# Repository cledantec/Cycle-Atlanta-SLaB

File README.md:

Cycle Atlanta: Seeing Like a Bike
================
[Atlanta's Data Science for Social Good (DSSG) 2017](http://dssg-atl.io/)
----------

The Cycle Atlanta project aims to create sensor systems that allow a bike to "see" its environment and collect data as a participatory effort to help the City of Atlanta make informed decisions about biking infrastructures. The team from Atlanta's Data Science for Social Good 2017 Summer program particularly worked on (1) reverse engineering all the prototypes developed separately by the LMC6650 team and consolidating all sensors into two microcontoller units (Raspberry Pi and Arduino) using the Master-Slave architecture; (2) identifying hardware/software bugs/flaws and refining systems iteratively; (3) implementing failure-tolerence techniques; (4) classifying environmental factors (to detect semantci-level objects) after collecting data using GoPro, voice recorders, and sensors; and (5) visualizing and analyzing the collected data using 3D models and machine learning techniques. 

## Documentations
* [System Overview](DSSG2017_doc/overview.md)
* [Hardware Systems (Electrical Devices and Circuits)](DSSG2017_doc/hardware.md)
* [Software Systems (Server Configurations and Scripts)](DSSG2017_doc/software.md)
* [Cases Design](DSSG2017_doc/cases.md)
* [Data Visualization (3D)](DSSG2017_doc/dataviz.md)
* [Data Analysis](DSSG2017_doc/data.md)
* [Backlog (Issues and Solutions)](DSSG2017_doc/backlog.md)

## Credits (DSSG)
### PI:
* [Dr. Christopher Le Dantec](https://ledantec.net/)

### DSSG Fellows:
* [Javier Argota](http://jard.us)
* [Myeong Lee](http://myeonglee.com)
* [Noel Mannariat](mailto:noelmannariat@gmail.com)
* [Erica Pantoja](mailto:ericapantoja1190@gmail.com)

### Special Thanks To:
* Dr. Kari Watkins
* Mariam Asad
* Bijan Tehrani
* Raj Lal
* Michael Vogel
* Bradley Rittenhouse

******

## [LMC6650: Seeing Like a Bike](http://ledantec.net/teaching/lmc-6650-spring-2017/)
### Spring 2017 Georgia Tech

LMC6650 students designed a custom PCB board for gas sensors, developed the Air Quality module and a data collection server on Raspberry Pi using RestAPIs, and implemented the proximity/serface quality sensor functionalities using Rapsberry Pi and Arduino. 

## Equipment used
* [Raspberry Pi](http://raspberrypi.org)
* [Arduino Uno](https://www.arduino.cc/en/Main/arduinoBoardUno)
* [Matrix One Creator](http://creator.matrix.one)
* [Anker 26800 mAh portable power bank](https://www.amazon.com/Anker-PowerCore-Portable-Double-Speed-Recharging/dp/B01JIWQPMW)
* [Knowles BU21771 contact microphone](www.digikey.com/product-detail/en/knowles/BU-21771-000/423-1004-ND/458515)
* Dimension ST768 for 3D printing

## Credits (LMC6650)
* **Air Quality team**: [Orianna Ott](https://www.linkedin.com/in/orianaott/) , [Lorina Navarro](https://www.linkedin.com/in/lmnavarro/) , [Reuben Fishback](https://www.linkedin.com/in/reuben-fishback-a4b31085/)
* **Proximity team**: [Sharon Ang](https://www.linkedin.com/in/sharon-ang/) , [Aastha Jalan](https://www.linkedin.com/in/aasthajalan/) , [Nikhil Soraba](https://www.linkedin.com/in/nikhil-soraba/)
* **Surface Quality team**: [Nene Igietseme](https://www.linkedin.com/in/nene-igietseme-19b65125/) , [Kristin Hare](https://www.linkedin.com/in/kristin-hare/) , [Shruti Dalvi](https://www.linkedin.com/in/shruti-dalvi/) , [Jayanth Mohana Krishna](https://linkedin.com/in/jayanthm)

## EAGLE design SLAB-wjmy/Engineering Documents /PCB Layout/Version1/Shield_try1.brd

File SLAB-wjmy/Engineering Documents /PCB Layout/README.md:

xTwo versions of the PCB designs are in the &quot;PCB Layout&quot; Folder.

You may download Eagle CAD software from AutoCAD and open it from the software.

This PCB is to provide stable connection from the micro-controller to Lidars. Version 1.0 used PWM transmission; Version 2.0 used I2C communication protocol. It is believed that Version 2.0 can measure much more accurately. However, due to the shelter-in-place situation, the testing was not able to conduct.

Version 1.0 - The original version that was printed and tested.

Pros: 1) Compact; 2) Easy to manufacture

Cons: 1) Lower sampling rate; 2) Power issue; 3) Wiring harness

Version 2.0 - The improved version that was designed by WJMY. The PCB layout was validated by the Electronics lab at Georgia Tech Mechanical Engineering Department.

Pros: 1) Estimated run time: 6 hours; 2) Easy assembly and disassembly;

3) Faster sampling rate

Cons: 1) Relatively more difficult to manufacture.

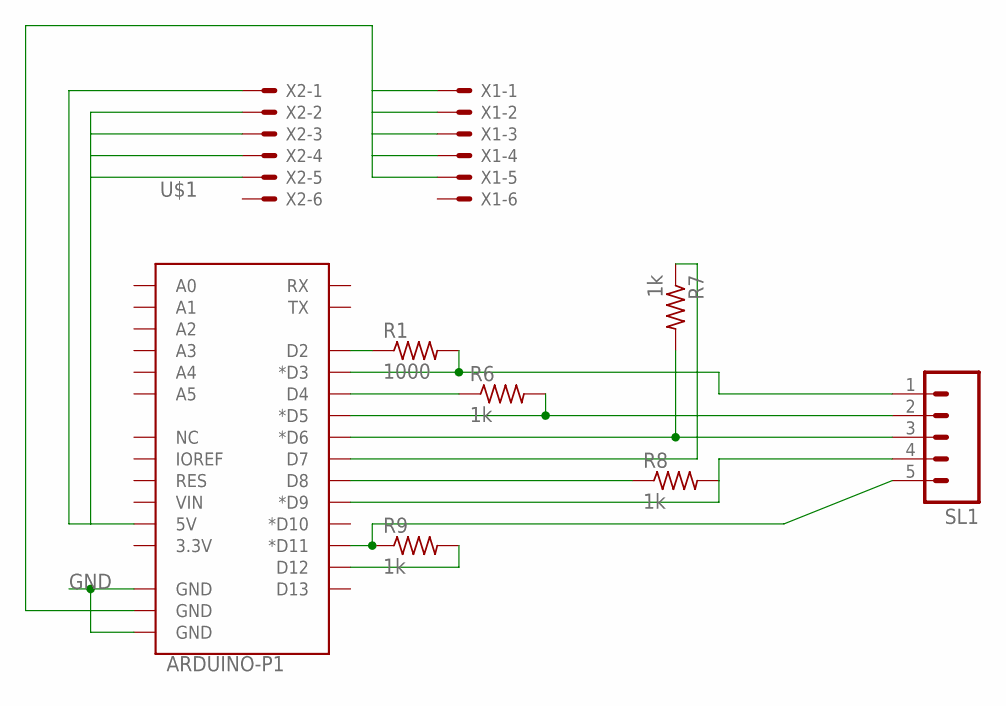
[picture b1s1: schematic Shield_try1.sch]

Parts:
R1: 1000; R0805
R6, R7, R8, R9: 1k; R0805
SL1: M05; 05P
U$1: ARDUINO-P1
X1, X2: 22-23-2061

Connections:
GND: U$1.GND@0 (GND), U$1.GND@1 (GND), U$1.GND@2 (GND), X1.1, X1.2, X1.3, X1.4, X1.5
unnamed: R1.2, SL1.1, U$1.D3 (*D3)
unnamed: R7.2, SL1.3, U$1.D6 (*D6)
unnamed: R6.1, U$1.D4
unnamed: R6.2, SL1.2, U$1.D5 (*D5)
unnamed: R7.1, U$1.D7
unnamed: R8.1, U$1.D8
unnamed: R8.2, SL1.4, U$1.D9 (*D9)
unnamed: R9.1, SL1.5, U$1.D11 (*D11)
unnamed: R9.2, U$1.D12
unnamed: R1.1, U$1.D2
unnamed: U$1.5V, X2.1, X2.2, X2.3, X2.4, X2.5

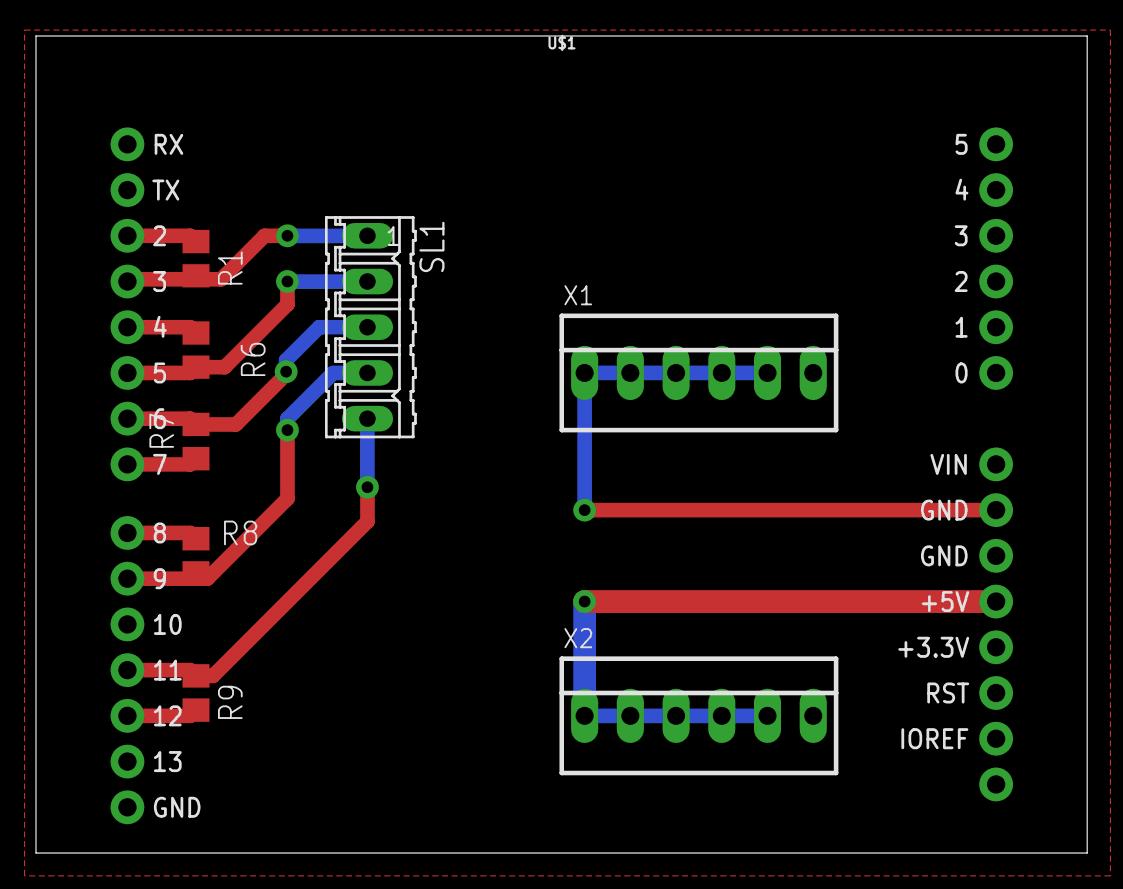
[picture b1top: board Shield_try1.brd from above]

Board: 2 copper layers, 58.4 x 45.4 mm, 9 parts (0 on the bottom side), 12 nets.

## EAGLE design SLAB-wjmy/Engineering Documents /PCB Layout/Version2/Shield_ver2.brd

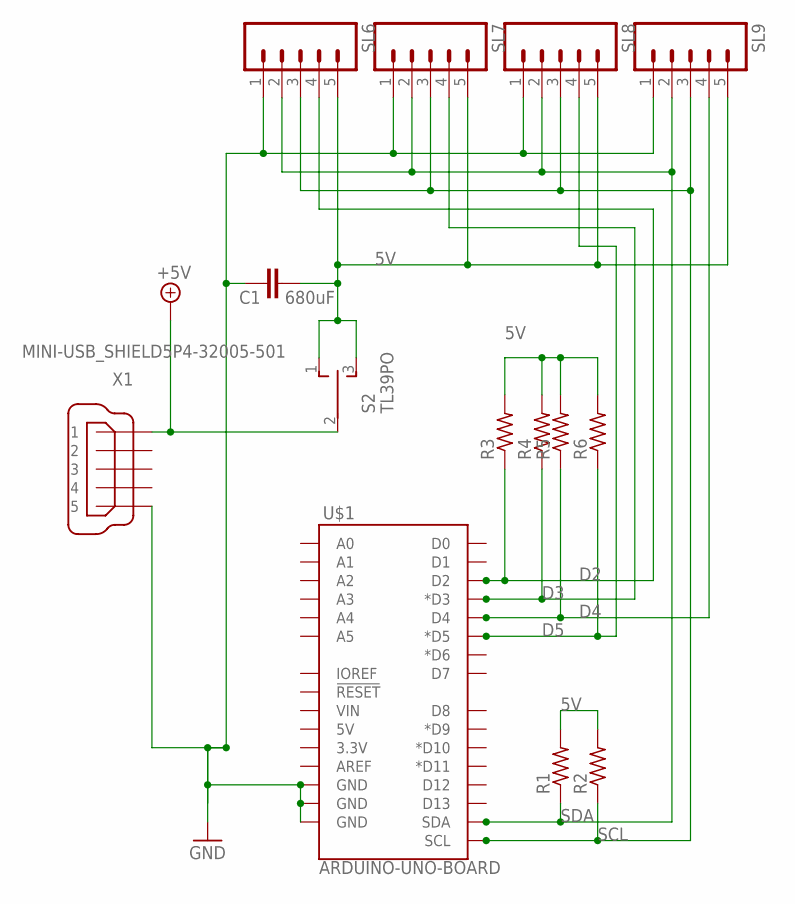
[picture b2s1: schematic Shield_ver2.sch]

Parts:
C1: 680uF; C5B2.5
R1, R2, R3, R4, R5, R6: R-US_R0805; R0805
S2: TL39PO; TL3XPO
SL6, SL7, SL8, SL9: M05; 05P
U$1: ARDUINO-UNO-BOARD
X1: MINI-USB_SHIELD5P4-32005-501; 32005-501

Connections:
5V: C1.2, R1.2, R2.2, R3.2, R4.2, R5.2, R6.2, S2.1 (O), S2.3 (S), SL6.5, SL7.5, SL8.5, SL9.5
+5V: S2.2, X1.1
D2: R3.1, SL6.4, U$1.D2
D3: R4.1, SL7.4, U$1.D3 (*D3)
D4: R5.1, SL9.4, U$1.D4
D5: R6.1, SL8.4, U$1.D5 (*D5)
GND: C1.1, SL6.1, SL7.1, SL8.1, SL9.1, U$1.GND@1 (GND), U$1.GND@2 (GND), U$1.GND@3 (GND), X1.5
SCL: R2.1, SL6.3, SL7.3, SL8.3, SL9.3, U$1.SCL
SDA: R1.1, SL6.2, SL7.2, SL8.2, SL9.2, U$1.SDA

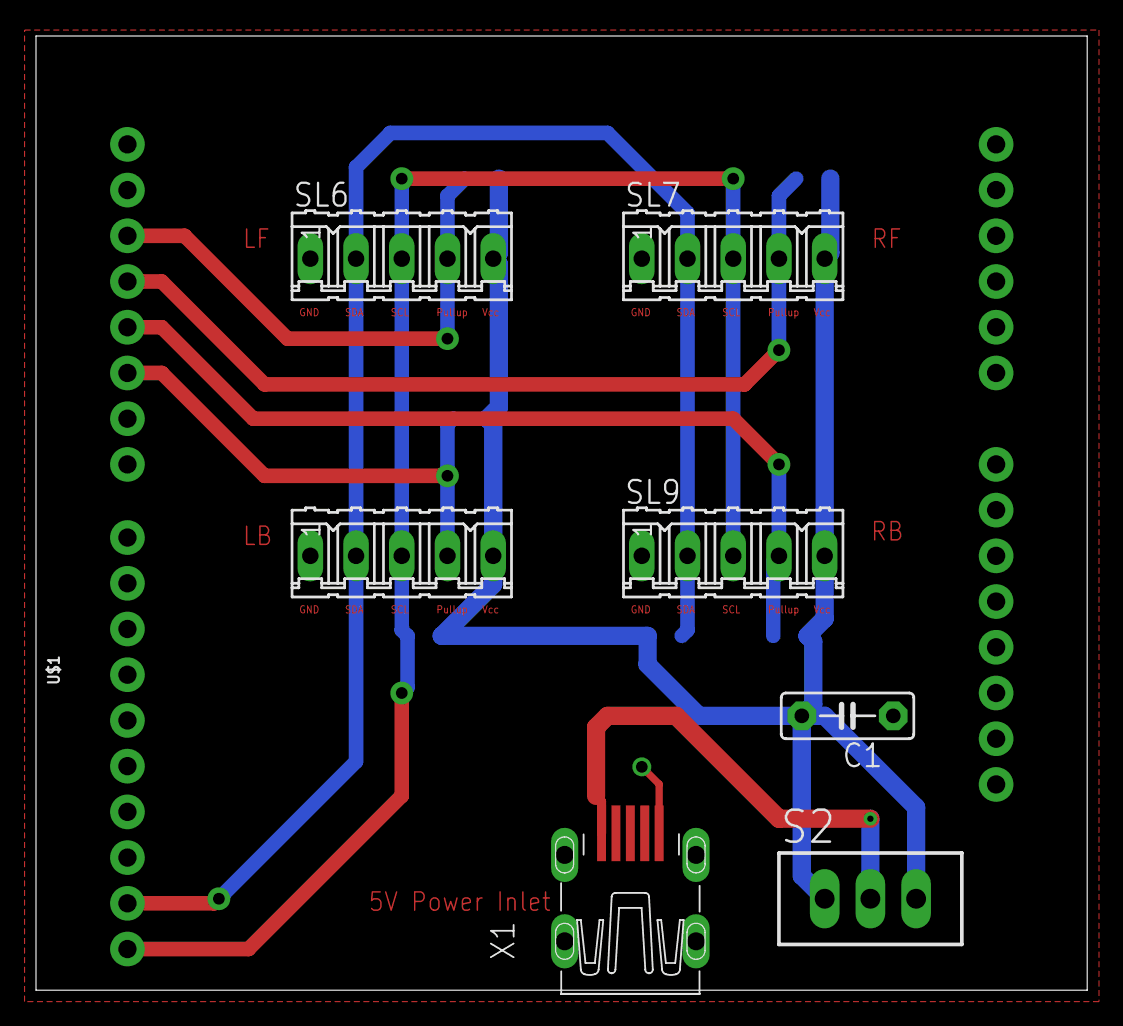
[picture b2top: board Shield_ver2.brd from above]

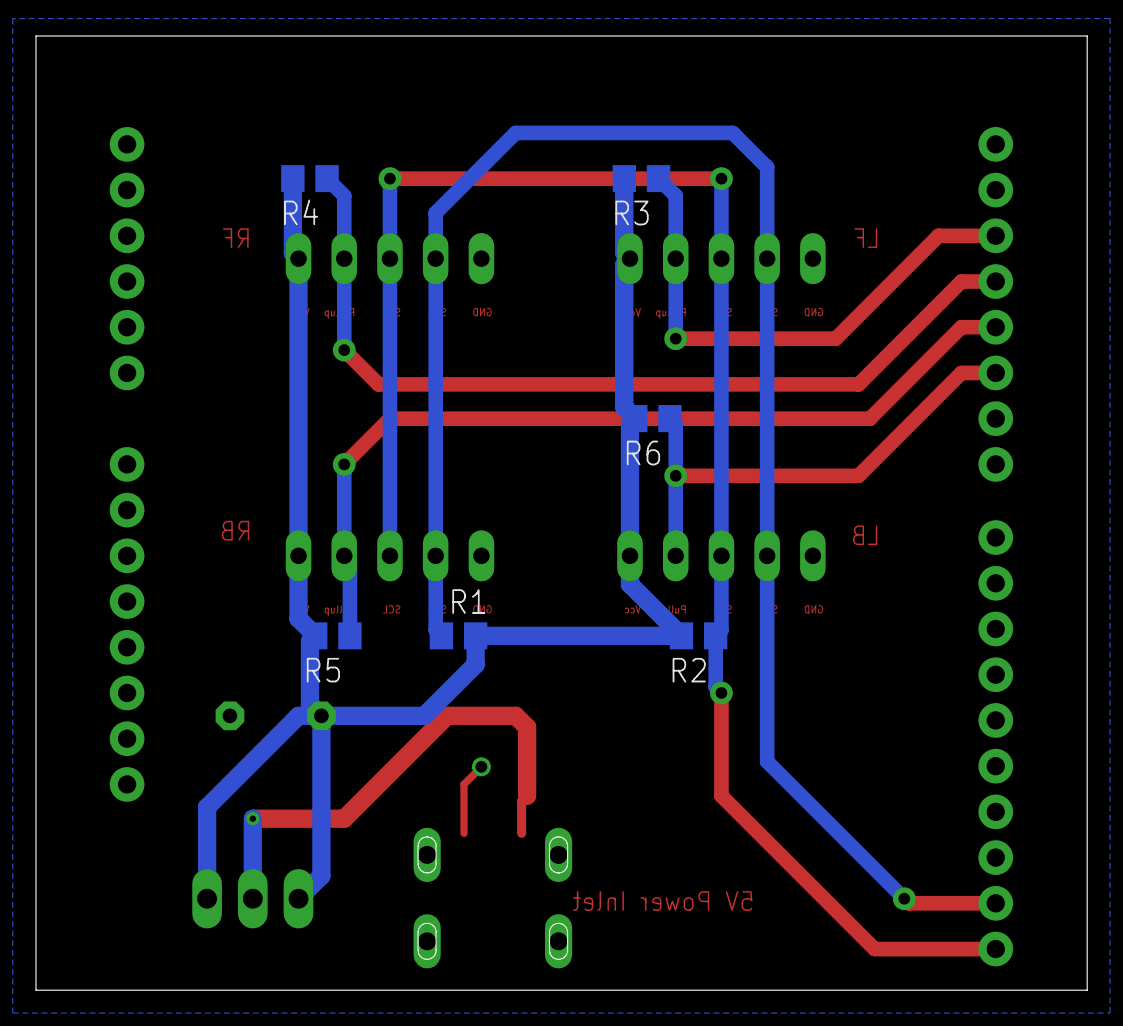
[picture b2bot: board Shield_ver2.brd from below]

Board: 2 copper layers, 58.4 x 53.0 mm, 14 parts (6 on the bottom side), 9 nets.

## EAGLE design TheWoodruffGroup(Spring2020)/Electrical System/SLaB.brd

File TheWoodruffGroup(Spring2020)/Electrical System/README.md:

# Electrical System Documentation
The electrical system includes the sensors and other electrical components used, as well as the PCB that connects them all. The electrical components include:
- 1x [Anker 5000 mAh Battery](https://www.anker.com/products/variant/powercore-5000/A1109011)
- 1x USB-A male-to-male cable
- 1x [Stewart Connector USB-A port](https://www.digikey.com/product-detail/en/stewart-connector/SS-52100-001/380-1412-ND/7902377)
- 1x On/Off Switch
- 1x Current Sensor
- 1x [Teensy 4.0 Microcontroller](https://www.pjrc.com/store/teensy40.html)
- 4x [Garmin LIDAR-Lite v4 LEDs](https://buy.garmin.com/en-US/US/p/610275)
- 1x [Adafruit Bluefruit UART Friend](https://www.adafruit.com/product/2479)
- 2x 1.5 kΩ (pull-up) resistors
- 1x 680 μF capacitor

The current PCB was designed in Eagle 9.6.1. Since Georgia Tech's [Electronics Lab](http://www.me.gatech.edu/facilities/electronic_lab) uses Eagle, PCBs can typically be manufactured within a day of the request if Eagle \*.brd files are submitted. For information on PCB design, I recommend [this tutorial by Brian Benchoff at Hackaday](https://hackaday.com/2016/09/22/making-a-pcb-eagle-part-1/). 

## Overview of Components
### Anker 5000 mAh Battery
This battery provides power to the Teensy and all of the components; it was sized based on the estimated current consumption of the device. It was calculated that the system will draw about 442 mA of current (2 mA from Bluetooth, 85 mA from each LIDAR, 100 from Teensy), so for a half-hour ride, only 221 mAh would be needed. Anker's 5000 mAh model was selected as the smallest and cheapest option, but other options may also be viable. The battery comes with a Micro-USB cable included for charging, but the micro-USB ports that I could find all seemed too small to easily solder to a PCB, so the board has a USB-A ("normal" USB) port instead, which are easier to solder, and still cheap & easy to find. Although the Teensy has a micro-USB port on it for power, connecting directly to this would make it impossible to measure the current draw, as the current sensor must be placed in series with the power source, so power must be provided through a separate USB port. 
The battery has a minimum current draw of 50 mA. We believe that the system will draw more than that, but **this would need to be verified experimentally**. 

### USB-A male-to-male cable
Since the board uses a USB-A port, a separate USB cable must be purchased to connect the battery to the board. A smaller cable would likely be best to prevent tangling. 

### Stewart Connector USB-A port
A USB-A port was chosen instead of a Micro-USB port because they appeared to be much easier to solder to a board, but any type of USB port should work, likely requiring changes to the footprint in the PCB file. This specific port was chosen because it was the cheapest one I could find on Digi-Key, but again, any USB port should work. 
The datasheet for this part did not specify which pin corresponded to what signal, so it had to be extrapolated based on similar connectors. **It needs to be verified experimentally which pin corresponds to 5V and which pin corresponds to ground**. 

### On/Off Switch 
This is a simple power switch to turn the device on or off, so that the battery power can be conserved when not in use. Any switch that holds its state and has leads attached to it can be used. Something like [this](https://www.adafruit.com/product/1092) would be fine, but the possibility of accidentally toggling the switch should be considered too, so a sliding switch might be better. The switch itself would be on the housing, and the leads coming off it would be soldered to the board. 

### Current Sensor 
The current sensor is used to estimate the current battery level by numerically integrating the current consumed over time. We never had the opportunity to test the current sensor, so everything involving it is entirely theoretical, including the wiring. The one used in the PCB is [this one from Allegro MicroSystems](https://www.digikey.com/product-detail/en/allegro-microsystems/ACS750LCA-050/ACS750LCA-050-ND/1006488), a default option provided in Eagle, which is now discontinued. It appears to have the same footprint as [this one](https://www.digikey.com/product-detail/en/allegro-microsystems/ACS770LCB-050B-PFF-T/620-1541-5-ND/4473980), which is still active. These current sensors may be bigger than we need, as they can sense up to 50 A of current, and the voltage outputted from them might be too low to be accurately read by the Teensy. **It may be better to use a different current sensor that is more suited to the range of currents being measured, and if the voltage is still too low, it may be best to amplify it with an op-amp.** It is also possible to calculate current by placing a small known resistor in series with the power source, where the current sensor would go, and measuring the voltage across it, but it is unclear how accurate this would be, and how much this would change the dynamics of the circuit. 

### Teensy 4.0 Microcontroller
This is the microcontroller that manages all of the sensors. It is faster and more powerful than an Arduino Uno, and should be fast enough to handle all the data being gathered. User-made Eagle libraries for the Teensy can be found [here](https://www.pjrc.com/teensy/eagle_lib.html), and the one used in this design is [the one by Constantin](https://forum.pjrc.com/threads/935-Eagle-library-with-Teensy-3-0-footprint?p=20178&viewfull=1#post20178) ("Teensy_3_and_LC_Series_Boards_v1.4.zip"). The Teensy 4.0 has largely the same pinout as the Teensy 3.2 and 3.1, so the Teensy 3.2/3.1 board available in the library is the footprint used in this design. The pins that are used all seem to be the same between 4.0 and 3.2, but **the wiring should be verified experimentally**. 

### Garmin LIDAR-Lite v4 LED
The LIDAR is used to measure the distance to various objects in the environment. Using multiple LIDARs, the speed of passing objects can be calculated. If two LIDARs are placed facing to one side of the bike with a known distance offset in the direction of motion, then the lag between the signals that the two LIDARs read can be used to calculate the speed of the passing object relative to the speed of the bike. This lag can be calculated with cross correlation, with the MATLAB function [xcorr()](https://www.mathworks.com/help/matlab/ref/xcorr.html), or the NumPy function [np.correlate()](https://numpy.org/doc/1.18/reference/generated/numpy.correlate.html), The distance between the LIDARs divided by the time lag between the signals is the speed of the passing object, relative to the bike. With an accurate measurement of the bike speed, coming from the app, the speed of the passing object relative to the ground can be calculated. Tests were done with the previous iteration of this device, [the v3](https://buy.garmin.com/en-US/US/p/557294), and it did not seem to be accurate enough, although only one device was tested. Regardless, it was decided to use the v4 because, according to the specs, it is more accurate, cheaper, and uses less power than its predecessor, however no tests could be done with it. The LIDARs communicate via I2C, and each one needs a different I2C address for proper communication. This can be done programatically with the [LIDAR-Lite Arduino Library](https://github.com/garmin/LIDARLite_Arduino_Library). The wiring was done based on their [specs sheet](http://static.garmin.com/pumac/LIDAR-Lite%20LED%20v4%20Instructions_EN-US.pdf) and comments in their example code, including the two resistors and the capacitor, so **it all needs to be verified experimentally**. 

### Adafruit Bluefruit UART Friend
This is the Bluetooth communication module that establishes a connection with the phone to send LIDAR data. It is not currently in the PCB as we had difficulties with reliably sending/receiving data. **Much more testing needs to be done with Bluetooth.** This device uses the Bluetooth Low Energy protocol, which is distinct from conventional Bluetooth. All the necessary information for this device can be found at the link above. 

## PCB design info
### PCB Files
There are 3 custom library files (\*.lbr) included in this folder: one for the LIDAR, one for the USB, and one for the Teensy. The Teensy library is the one mentioned above, and the other two are simple ones that I made, as I couldn't find EAGLE files for them online. The .brd file is the PCB layout, the .sch file is the schematic, and the .step file is a 3D model used in the CAD. 
### LIDAR Connection
The LIDAR footprint is just 10 holes in two rows spaced 0.1" apart, since the LIDAR itself doesn't have any method of connecting to a board. A port like [this](https://flytron.com/connectorscables/254-10-pin-isp-male-connector-header.html) could be soldered on, and then a ribbon cable soldered to the LIDAR with a plug on the other side could be used to easily connect to the board.

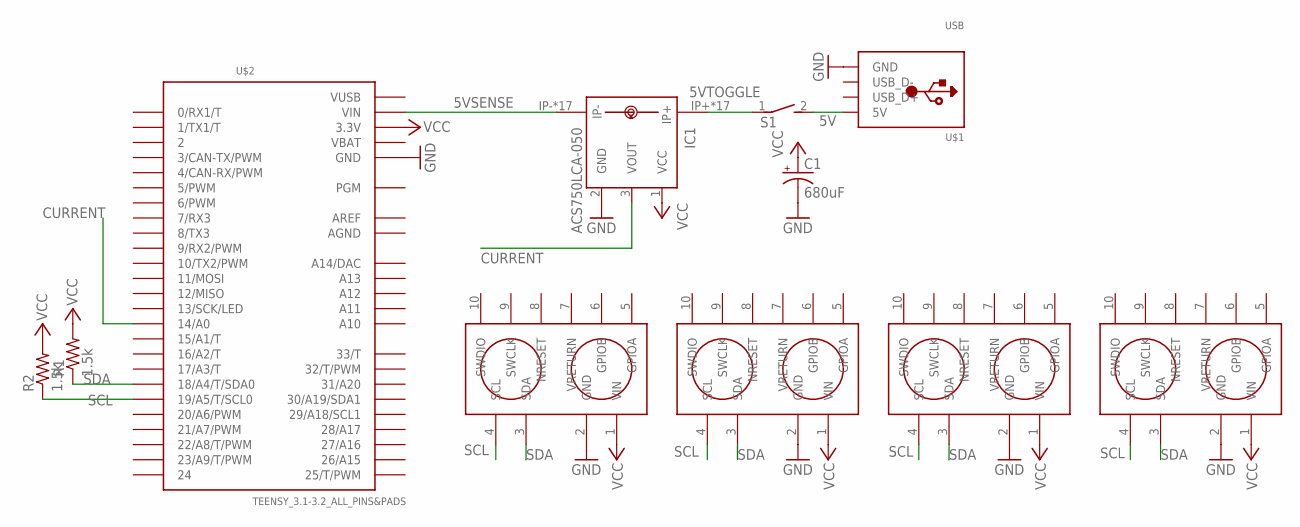
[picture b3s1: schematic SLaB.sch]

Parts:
C1: 680uF; E2-5
IC1: ACS750LCA-050; ACS75050
R1, R2: 1.5k; 0204/7
S1: DS01E; DS-01
U$1: USB
U$2: TEENSY_3.1-3.2_ALL_PINS&PADS; TEENSY_3.0-3.2_ALL_PINS_&_PADS
U$3, U$4, U$5, U$6: LIDAR

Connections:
5V: S1.2, U$1.5V
5VSENSE: IC1.IP-, IC1.IP-@2 (IP-), IC1.IP-@3 (IP-), IC1.IP-@4 (IP-), IC1.IP-@5 (IP-), IC1.IP-@6 (IP-), IC1.IP-@7 (IP-), IC1.IP-@8 (IP-), IC1.IP-@9 (IP-), IC1.IP-@10 (IP-), IC1.IP-@11 (IP-), IC1.IP-@12 (IP-), IC1.IP-@13 (IP-), IC1.IP-@14 (IP-), IC1.IP-@15 (IP-), IC1.IP-@16 (IP-), IC1.IP-@17 (IP-), U$2.VIN
5VTOGGLE: IC1.IP+, IC1.IP+@2 (IP+), IC1.IP+@3 (IP+), IC1.IP+@4 (IP+), IC1.IP+@5 (IP+), IC1.IP+@6 (IP+), IC1.IP+@7 (IP+), IC1.IP+@8 (IP+), IC1.IP+@9 (IP+), IC1.IP+@10 (IP+), IC1.IP+@11 (IP+), IC1.IP+@12 (IP+), IC1.IP+@13 (IP+), IC1.IP+@14 (IP+), IC1.IP+@15 (IP+), IC1.IP+@16 (IP+), IC1.IP+@17 (IP+), S1.1
AGND: U$2.AGND
AREF: U$2.AREF
CURRENT: IC1.3 (VOUT), U$2.14/A0
GND: C1.-, IC1.2 (GND), U$1.GND, U$2.GND, U$2.GND1 (GND), U$2.GND2 (GND), U$3.2 (GND), U$4.2 (GND), U$5.2 (GND), U$6.2 (GND)
SCL: R2.1, U$2.19/A5 (19/A5/T/SCL0), U$3.4 (SCL), U$4.4 (SCL), U$5.4 (SCL), U$6.4 (SCL)
SDA: R1.1, U$2.18/A4 (18/A4/T/SDA0), U$3.3 (SDA), U$4.3 (SDA), U$5.3 (SDA), U$6.3 (SDA)
VBAT: U$2.VBAT
VCC: C1.+, IC1.1 (VCC), R1.2, R2.2, U$2.3.3V, U$2.3.3V1 (3.3V), U$2.3.3V2 (3.3V), U$3.1 (VIN), U$4.1 (VIN), U$5.1 (VIN), U$6.1 (VIN)
VUSB: U$2.VUSB

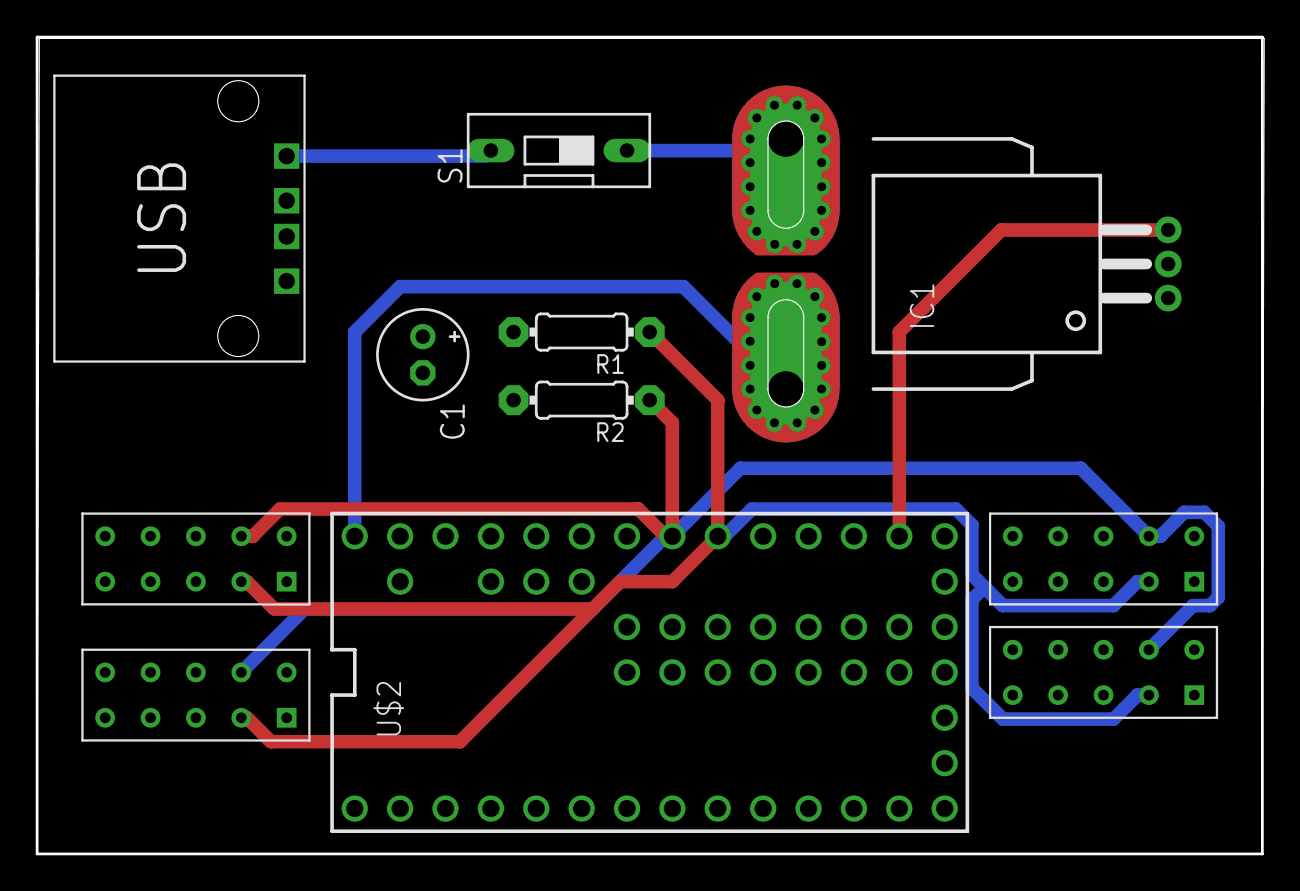
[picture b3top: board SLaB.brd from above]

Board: 2 copper layers, 68.7 x 45.7 mm, 11 parts (0 on the bottom side), 8 nets.

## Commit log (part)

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2017-04-22 Surface quality initial commit - package.json has all the Node modules needed - *_server.js scripts are NodeJS clients that send the server data - added data cleanup script, output CSV, tableau analy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
2017-04-22 Air Quality initial commit
2017-04-22 Added more images GoPro straight mount STL
2017-04-22 readme.md changes
2017-04-23 Added comments to server code
2017-04-24 Added opencv code to surface
2017-04-24 Added Air Quality endpoints
2017-04-24 Proximity files
    All the source code used by the proximity team to collect data from
    ultrasound and lidar sensors.
2017-04-26 Server documentation uploaded
2017-05-17 Adjusted error message & updated readme
2017-05-25 Re-org
    Major reorg of each component. Re-writing code for AQ.
2017-05-25 .DS_Store banished!
2017-05-25 Remove .idea
2017-05-31 Python scripts that operate sensors on the Matrix board
2017-06-09 Add files via upload
    Code for gps using USB
2017-06-12 changes in Arduino files
2017-06-12 added distance0 and libraries
2017-06-12 new server files
2017-06-12 arduino file updated
2017-06-14 Sensor receiver added
2017-06-15 LED enabled. Serial communication refined
2017-06-16 GPS and Sensors work together (+ LEDs)
2017-06-16 LED complete. All sensors work together fine. Sensor resolution adjusted
2017-06-20 styling
2017-06-27 Reset functionality implemented in Raspberry Pi and Arduion. Sync issue resolved. USB ports fixed for serial communications
2017-06-27 time interval to 0.1 sec
2017-06-27 sample 10 min data
2017-06-27 removed Null values
2017-06-28 descriptive graphs
2017-06-28 stamen map added
2017-07-07 Gas sensor testbed added
2017-07-07 a new gas calibration data
2017-07-11 gas boards 4,5,7 added
2017-07-11 R script added
2017-07-12 gas sensor graphs
2017-07-13 Mariam's test ruriding data
2017-07-14 Gas station data added
2017-07-15 Time-series speed graph
2017-07-18 some code inhancement and signautre data
2017-07-18 Arduino sync issue resolved
2017-07-18 parameter changed. official gas station data added
2017-07-18 re-indexing
2017-07-18 sidewalk riding data added
2017-07-18 Jeremy's recent data
2017-07-18 CO and SO2 added
2017-07-19 data order
2017-07-19 Signature data with corrected sonar sensors
2017-07-20 added 0719 riding for signatures
2017-07-20 signature examples
2017-07-20 proximity data updated for 0719
2017-07-20 new data and signatures
2017-07-21 graphs and new sig data
2017-07-21 Mariam's 0720 dataata
2017-07-21 Jeremy's 0721 data
2017-07-21 gas aggregated to 0718 data
2017-07-21 Prox and GPS joined for Jeremy's 0721:
2017-07-21 Signatures
2017-07-22 gas calibration graphs
2017-07-22 Mariam's 0720 joined data
2017-07-22 Create All_Graphs
2017-07-22 Create akk
2017-07-22 Javier's 0722
2017-07-22 0722 Javier's Join table
2017-07-22 A folder deleted
2017-07-22 Updated Signatures
2017-07-22 Use These (Updated)
2017-07-22 deleted unnecessary files
2017-07-22 0722 Signatures Added
2017-07-22 deleted a folder
2017-07-22 0722 Signatures
2017-07-23 Create 2207_SignaturesErica
2017-07-23 Same route data on 0723
2017-07-23 Create files
2017-07-23 distance-based data
2017-07-23 csv clean up
2017-07-23 gps proximity joined for the same route riding 0722
2017-07-23 change of locations
2017-07-23 distance-based resampling
2017-07-24 Signature
2017-07-24 first part of 0722, resampled for all variables
2017-07-24 random classifires added for testing
2017-07-24 random classifiers for both sides
2017-07-24 day-time added
2017-07-24 classification data
2017-07-24 classifications
2017-07-24 data processing graphs
2017-07-25 Readme for the front page
2017-07-25 typo
2017-07-25 modifications in MD
2017-07-25 fixed links
2017-07-25 removed blank
2017-07-25 mailto
2017-07-26 Doc skeletons
2017-07-26 docs..
2017-07-26 MD link corrected
2017-07-26 viz doc added
2017-07-26 added Myeong's name
2017-07-26 test mod
2017-07-26 added Noel's name
2017-07-26 added Erica's name
2017-07-26 matrix image
2017-07-26 basic viz page
2017-07-26 basic viz page information 2
2017-07-27 system overview
2017-07-27 classifiers data
2017-07-27 data analysis draft
2017-07-27 formatting
2017-07-27 Rhino folder added and Grasshopper definition + viz webpage update
2017-07-27 viz webpage updating
2017-07-27 viz webpage update + gh file update
2017-07-27 hardware agenda
2017-07-27 gps image
2017-07-27 gpsStructure image
2017-07-27 gasSensor Image
2017-07-27 data analysis
2017-07-27 image path corrected
2017-07-28 sensorInfo
2017-07-28 imgs and folders for PCB
2017-07-28 folders for ABS box + doc for back box
2017-07-28 create ABS boxes md file
2017-07-28 Rename ABS_laser_cutting to ABS_laser_cutting.md
2017-07-28 gpsStructure_Image
2017-07-28 Rename ABS_laser_cutting.md to README.md
2017-07-28 update README back box
2017-07-28 hardware update
2017-07-28 adding PCB image
2017-07-28 software doc addoc added. John's data added
2017-07-28 Added Case folder
2017-07-28 Added images
2017-07-28 Added Case doc
2017-07-28 gas documentation
2017-07-28 doc first draft
2017-07-28 links
2017-09-22 fixing youtube video link on hardware page
2018-08-22 Adding code from Summer 2018
2018-08-22 Added readme for CDS 2018
2019-05-03 All Scripts Created Fall 18 - Spring 19
    All of the scripts created from Fall 2018 to Spring 2019 are included along with a readme that explains how to run them and what they are for.
2020-04-12 TheWoodruffGroup Capstone Android App
2020-04-13 Create README.md
    Documentation for Spring 2020 Capstone project for The Woodruff Group
2020-04-14 Edited package name
2020-04-14 Enlarged button text size
2020-04-14 Updated contact info
2020-04-15 Changed folder structure
2020-04-15 Added mechanical and electrical documentation files
2020-04-15 Added Bluetooth test app
2020-04-24 Added electrical files and documentation
2020-04-24 Fixed electrical documentation formatting
2020-04-30 feat: add wjmy
2020-05-02 Bump acorn from 6.4.0 to 6.4.1 in /SLAB-wjmy/wjmy-app
    Bumps [acorn](https://github.com/acornjs/acorn) from 6.4.0 to 6.4.1.
    - [Release notes](https://github.com/acornjs/acorn/releases)
    - [Commits](https://github.com/acornjs/acorn/compare/6.4.0...6.4.1)
2020-07-20 Bump lodash from 4.17.15 to 4.17.19 in /SLAB-wjmy/wjmy-app
    Bumps [lodash](https://github.com/lodash/lodash) from 4.17.15 to 4.17.19.
    - [Release notes](https://github.com/lodash/lodash/releases)
    - [Commits](https://github.com/lodash/lodash/compare/4.17.15...4.17.19)
2021-03-31 Bump y18n from 3.2.1 to 3.2.2 in /SLAB-wjmy/wjmy-app
    Bumps [y18n](https://github.com/yargs/y18n) from 3.2.1 to 3.2.2.
    - [Release notes](https://github.com/yargs/y18n/releases)
    - [Changelog](https://github.com/yargs/y18n/blob/master/CHANGELOG.md)
    - [Commits](https://github.com/yargs/y18n/commits)
2021-05-07 Bump ua-parser-js from 0.7.21 to 0.7.28 in /SLAB-wjmy/wjmy-app
    Bumps [ua-parser-js](https://github.com/faisalman/ua-parser-js) from 0.7.21 to 0.7.28.
    - [Release notes](https://github.com/faisalman/ua-parser-js/releases)
    - [Commits](https://github.com/faisalman/ua-parser-js/compare/0.7.21...0.7.28)
2021-05-11 Bump lodash from 4.17.15 to 4.17.21 in /SLAB-wjmy/wjmy-app
    Bumps [lodash](https://github.com/lodash/lodash) from 4.17.15 to 4.17.21.
    - [Release notes](https://github.com/lodash/lodash/releases)
    - [Commits](https://github.com/lodash/lodash/compare/4.17.15...4.17.21)
2021-05-11 Bump hosted-git-info from 2.8.5 to 2.8.9 in /SLAB-wjmy/wjmy-app
    Bumps [hosted-git-info](https://github.com/npm/hosted-git-info) from 2.8.5 to 2.8.9.
    - [Release notes](https://github.com/npm/hosted-git-info/releases)
    - [Changelog](https://github.com/npm/hosted-git-info/blob/v2.8.9/CHANGELOG.md)
    - [Commits](https://github.com/npm/hosted-git-info/compare/v2.8.5...v2.8.9)
2021-06-11 Bump glob-parent from 5.1.0 to 5.1.2 in /SLAB-wjmy/wjmy-app
    Bumps [glob-parent](https://github.com/gulpjs/glob-parent) from 5.1.0 to 5.1.2.
    - [Release notes](https://github.com/gulpjs/glob-parent/releases)
    - [Changelog](https://github.com/gulpjs/glob-parent/blob/main/CHANGELOG.md)
    - [Commits](https://github.com/gulpjs/glob-parent/compare/v5.1.0...v5.1.2)
    ---
    updated-dependencies:
2021-08-12 Bump path-parse from 1.0.6 to 1.0.7 in /SLAB-wjmy/wjmy-app
    Bumps [path-parse](https://github.com/jbgutierrez/path-parse) from 1.0.6 to 1.0.7.
    - [Release notes](https://github.com/jbgutierrez/path-parse/releases)
    - [Commits](https://github.com/jbgutierrez/path-parse/commits/v1.0.7)
    ---
    updated-dependencies:
    - dependency-name: path-parse
2021-09-21 Bump tmpl from 1.0.4 to 1.0.5 in /SLAB-wjmy/wjmy-app
    Bumps [tmpl](https://github.com/daaku/nodejs-tmpl) from 1.0.4 to 1.0.5.
    - [Release notes](https://github.com/daaku/nodejs-tmpl/releases)
    - [Commits](https://github.com/daaku/nodejs-tmpl/commits/v1.0.5)
    ---
    updated-dependencies:
    - dependency-name: tmpl
2022-02-13 Bump ajv from 6.11.0 to 6.12.6 in /SLAB-wjmy/wjmy-app
    Bumps [ajv](https://github.com/ajv-validator/ajv) from 6.11.0 to 6.12.6.
    - [Release notes](https://github.com/ajv-validator/ajv/releases)
    - [Commits](https://github.com/ajv-validator/ajv/compare/v6.11.0...v6.12.6)
    ---
    updated-dependencies:
    - dependency-name: ajv
2022-03-02 Bump plist from 3.0.1 to 3.0.4 in /SLAB-wjmy/wjmy-app
    Bumps [plist](https://github.com/TooTallNate/node-plist) from 3.0.1 to 3.0.4.
    - [Release notes](https://github.com/TooTallNate/node-plist/releases)
    - [Changelog](https://github.com/TooTallNate/plist.js/blob/master/History.md)
    - [Commits](https://github.com/TooTallNate/node-plist/commits)
    ---
    updated-dependencies:
2022-04-29 Bump async from 2.6.3 to 2.6.4 in /SLAB-wjmy/wjmy-app
    Bumps [async](https://github.com/caolan/async) from 2.6.3 to 2.6.4.
    - [Release notes](https://github.com/caolan/async/releases)
    - [Changelog](https://github.com/caolan/async/blob/v2.6.4/CHANGELOG.md)
    - [Commits](https://github.com/caolan/async/compare/v2.6.3...v2.6.4)
    ---
    updated-dependencies:
2022-06-02 Bump simple-plist from 1.1.0 to 1.3.1 in /SLAB-wjmy/wjmy-app
    Bumps [simple-plist](https://github.com/wollardj/simple-plist) from 1.1.0 to 1.3.1.
    - [Release notes](https://github.com/wollardj/simple-plist/releases)
    - [Commits](https://github.com/wollardj/simple-plist/compare/1.1.0...v1.3.1)
    ---
    updated-dependencies:
    - dependency-name: simple-plist
2022-10-12 Bump xmldom and plist in /SLAB-wjmy/wjmy-app
    Removes [xmldom](https://github.com/xmldom/xmldom). It's no longer used after updating ancestor dependency [plist](https://github.com/TooTallNate/node-plist). These dependencies need to be updated to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
    Removes `xmldom`
    Updates `plist` from 3.0.1 to 3.0.6
    - [Release notes](https://github.com/TooTallNate/node-plist/releases)
    - [Changelog](https://github.com/TooTallNate/plist.js/blob/master/History.md)
    - [Commits](https://github.com/TooTallNate/node-plist/commits)
2022-10-20 Bump react-native-reanimated from 1.7.0 to 2.10.0 in /SLAB-wjmy/wjmy-app
    Bumps [react-native-reanimated](https://github.com/software-mansion/react-native-reanimated) from 1.7.0 to 2.10.0.
    - [Release notes](https://github.com/software-mansion/react-native-reanimated/releases)
    - [Commits](https://github.com/software-mansion/react-native-reanimated/compare/1.7.0...2.10.0)
    ---
    updated-dependencies:
    - dependency-name: react-native-reanimated
2022-12-11 Bump qs from 6.9.1 to 6.9.7 in /SLAB-wjmy/wjmy-app
    Bumps [qs](https://github.com/ljharb/qs) from 6.9.1 to 6.9.7.
    - [Release notes](https://github.com/ljharb/qs/releases)
    - [Changelog](https://github.com/ljharb/qs/blob/main/CHANGELOG.md)
    - [Commits](https://github.com/ljharb/qs/compare/v6.9.1...v6.9.7)
    ---
    updated-dependencies:
